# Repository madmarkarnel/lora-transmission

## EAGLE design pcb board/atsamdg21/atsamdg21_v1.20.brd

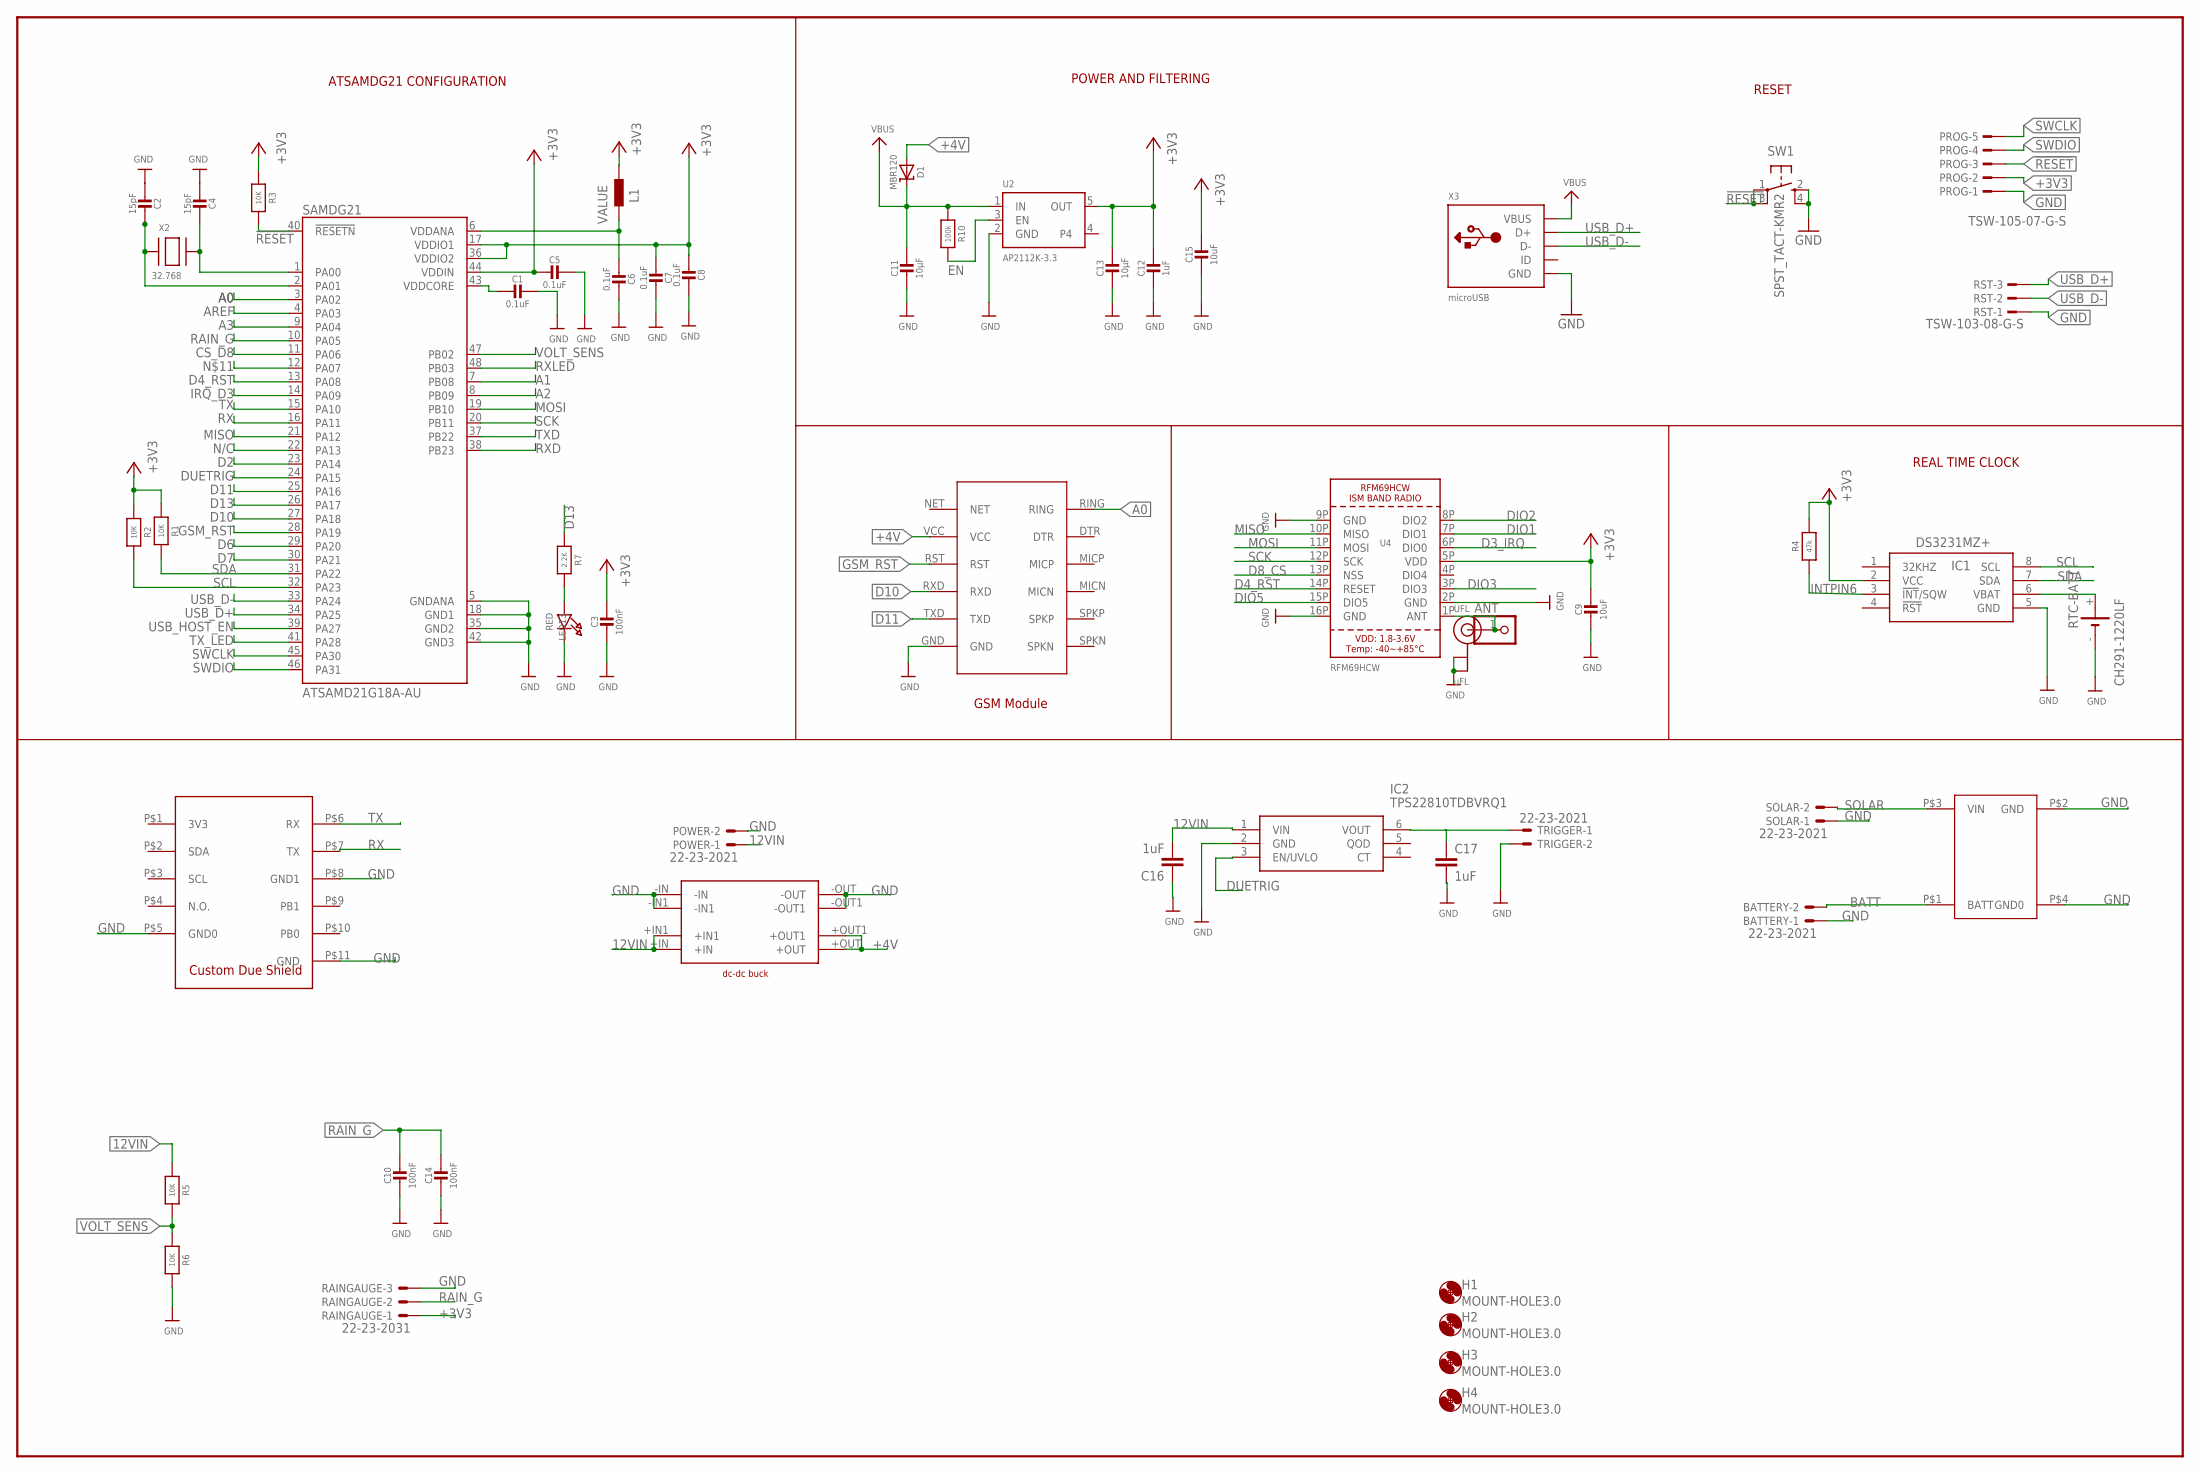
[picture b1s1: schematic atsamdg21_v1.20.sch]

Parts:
ANT: HEADER-1X1ROUND; 1X01_ROUND
BATTERY: 22-23-2021
C1, C5, C6, C7, C8: 0.1uF; 0603-NO
C2, C4: 15pF; 0603-NO
C3, C10, C14: 100nF; 0603-NO
C9, C15: 10uF; 0805-NO
C11, C13: 10µF; 0805-NO
C12: 1uF; 0603-NO
C16, C17: 1uF; C0603
D1: MBR120; SOD-123
H1, H2, H3, H4: MOUNT-HOLE3.0; 3,0
IC1: DS3231MZ+; SOIC127P600X175-8N
IC2: TPS22810TDBVRQ1; SOT95P280X145-6N
L1: BLM15HB121SN1; 0402
LED13: RED; CHIPLED_0805_NOOUTLINE
POWER: 22-23-2021
PROG: TSW-105-07-G-S; TSW-105-XX-G-S
R1, R2, R3, R5, R6: 10K; 0603-NO
R4: 47k; 0603-NO
R7: 2.2K; 0603-NO
R10: 100k; 0603-NO
RAINGAUGE: 22-23-2031
RST: TSW-103-08-G-S; TSW-103-XX-G-S
RTC-BATT: CH291-1220LF
SAMDG21: ATSAMD21G18A-AU; QFP50P900X900X120-48N
SOLAR: 22-23-2021
SW1: SPST_TACT-KMR2; KMR2
TRIGGER: 22-23-2021
U2: AP2112K-3.3; SOT23-5
U4: RFM69HCW; RFMHCW_SMT
U$7: SIM800L_MODULE; SIM800L
U$19: DC-DC_BUCK_MAD; DC-DC_BUCK
U$20: DUE_PADSDUE_GSM; DUESHIELD_BIG
U$36: LI-ION-CHARGER; LI-ION
UFL: uFL; U.FL
X2: 32.768; XTAL3215
X3: microUSB; 4UCONN_20329_V2

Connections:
12VIN: C16.2, IC2.1 (VIN), POWER.1, R5.1, U$19.+IN, U$19.+IN1
!RESET: PROG.3, R3.2, SAMDG21.40 (!RESETN), SW1.1, SW1.3 (P1)
+3V3: C3.1, C5.2, C7.2, C8.2, C9.1, C12.1, C13.1, C15.1, IC1.2 (VCC), L1.1, PROG.2, R1.1, R2.1, R3.1, R4.2, RAINGAUGE.1, SAMDG21.17 (VDDIO1), SAMDG21.36 (VDDIO2), SAMDG21.44 (VDDIN), U2.5 (OUT), U4.5P (VDD)
+4V: D1.A, U$7.VCC, U$19.+OUT, U$19.+OUT1
A0: SAMDG21.3 (PA02), U$7.RING
A1: SAMDG21.7 (PB08)
A2: SAMDG21.8 (PB09)
A3: SAMDG21.9 (PA04)
ANT: ANT.1, U4.1P (ANT), UFL.3 (SIGNAL)
AREF: SAMDG21.4 (PA03)
BATT: BATTERY.2, U$36.P$1 (BATT)
CS_D8: SAMDG21.11 (PA06)
D2: SAMDG21.23 (PA14)
D3_IRQ: U4.6P (DIO0)
D4_RST: SAMDG21.13 (PA08), U4.14P (RESET)
D6: SAMDG21.29 (PA20)
D7: SAMDG21.30 (PA21)
D8_CS: U4.13P (NSS)
D10: SAMDG21.27 (PA18), U$7.RXD
D11: SAMDG21.25 (PA16), U$7.TXD
D13: R7.1, SAMDG21.26 (PA17)
DIO1: U4.7P (DIO1)
DIO2: U4.8P (DIO2)
DIO3: U4.3P (DIO3)
DIO5: U4.15P (DIO5)
DUETRIG: IC2.3 (EN/UVLO), SAMDG21.24 (PA15)
EN: R10.2, U2.3 (EN)
GND: BATTERY.1, C1.1, C2.2, C3.2, C4.2, C5.1, C6.1, C7.1, C8.1, C9.2, C10.2, C11.2, C12.2, C13.2, C14.2, C15.2, C16.1, C17.2, IC1.5 (GND), IC2.2 (GND), LED13.C, POWER.2, PROG.1, R6.2, RAINGAUGE.3, RST.1, RTC-BATT.-, SAMDG21.5 (GNDANA), SAMDG21.18 (GND1), SAMDG21.35 (GND2), SAMDG21.42 (GND3), SOLAR.1, SW1.2 (S), SW1.4 (S1), TRIGGER.2, U2.2 (GND), U4.2P (GND), U4.9P (GND), U4.16P (GND), U$7.GND, U$19.-IN, U$19.-IN1, U$19.-OUT, U$19.-OUT1, U$20.P$5 (GND0), U$20.P$8 (GND1), U$20.P$11 (GND), U$36.P$2 (GND), U$36.P$4 (GND0), UFL.1 (GND), UFL.2 (GND), X3.BASE@1 (GND), X3.BASE@2 (GND), X3.GND, X3.SPRT@1 (GND), X3.SPRT@2 (GND), X3.SPRT@3 (GND), X3.SPRT@4 (GND)
GSM_RST: SAMDG21.28 (PA19), U$7.RST
INTPIN6: IC1.3 (!INT!/SQW), R4.1
IRQ_D3: SAMDG21.14 (PA09)
MISO: SAMDG21.21 (PA12), U4.10P (MISO)
MOSI: SAMDG21.19 (PB10), U4.11P (MOSI)
unnamed: C1.2, SAMDG21.43 (VDDCORE)
unnamed: IC1.6 (VBAT), RTC-BATT.+
unnamed: C6.2, L1.2, SAMDG21.6 (VDDANA)
unnamed: C2.1, SAMDG21.2 (PA01), X2.P$1
unnamed: C17.1, IC2.6 (VOUT), TRIGGER.1
unnamed: C4.1, SAMDG21.1 (PA00), X2.P$2
unnamed: LED13.A, R7.2
N/C: SAMDG21.22 (PA13)
RAIN_G: C10.1, C14.1, RAINGAUGE.2, SAMDG21.10 (PA05)
RX: SAMDG21.16 (PA11), U$20.P$7 (TX)
RXD: SAMDG21.38 (PB23)
RXLED: SAMDG21.48 (PB03)
SCK: SAMDG21.20 (PB11), U4.12P (SCK)
SCL: IC1.8 (SCL), R2.2, SAMDG21.32 (PA23)
SDA: IC1.7 (SDA), R1.2, SAMDG21.31 (PA22)
SOLAR: SOLAR.2, U$36.P$3 (VIN)
SWCLK: PROG.5, SAMDG21.45 (PA30)
SWDIO: PROG.4, SAMDG21.46 (PA31)
TX: SAMDG21.15 (PA10), U$20.P$6 (RX)
TXD: SAMDG21.37 (PB22)
TX_LED: SAMDG21.41 (PA28)
USB_D+: RST.3, SAMDG21.34 (PA25), X3.D+
USB_D-: RST.2, SAMDG21.33 (PA24), X3.D-
USB_HOST_EN: SAMDG21.39 (PA27)
VBUS: C11.1, D1.C, R10.1, U2.1 (IN), X3.VBUS
VOLT_SENS: R5.2, R6.1, SAMDG21.47 (PB02)

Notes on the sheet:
GSM Module
POWER AND FILTERING
RESET
ATSAMDG21 CONFIGURATION
REAL TIME CLOCK

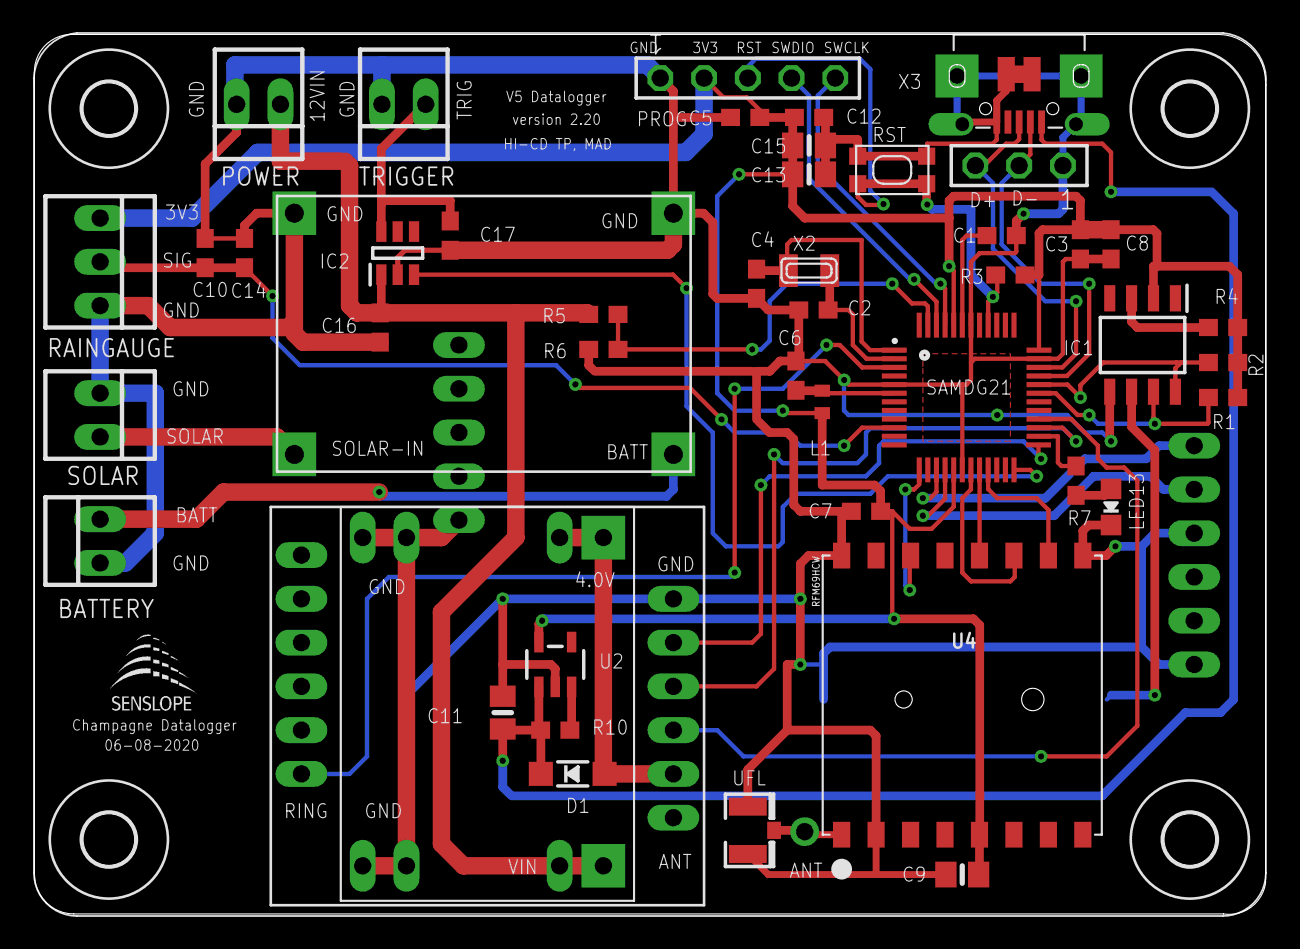
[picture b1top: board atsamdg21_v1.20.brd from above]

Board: 2 copper layers, 71.5 x 51.1 mm, 55 parts (1 on the bottom side), 38 nets.

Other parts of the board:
U$24: LOGO_SML_TNAME

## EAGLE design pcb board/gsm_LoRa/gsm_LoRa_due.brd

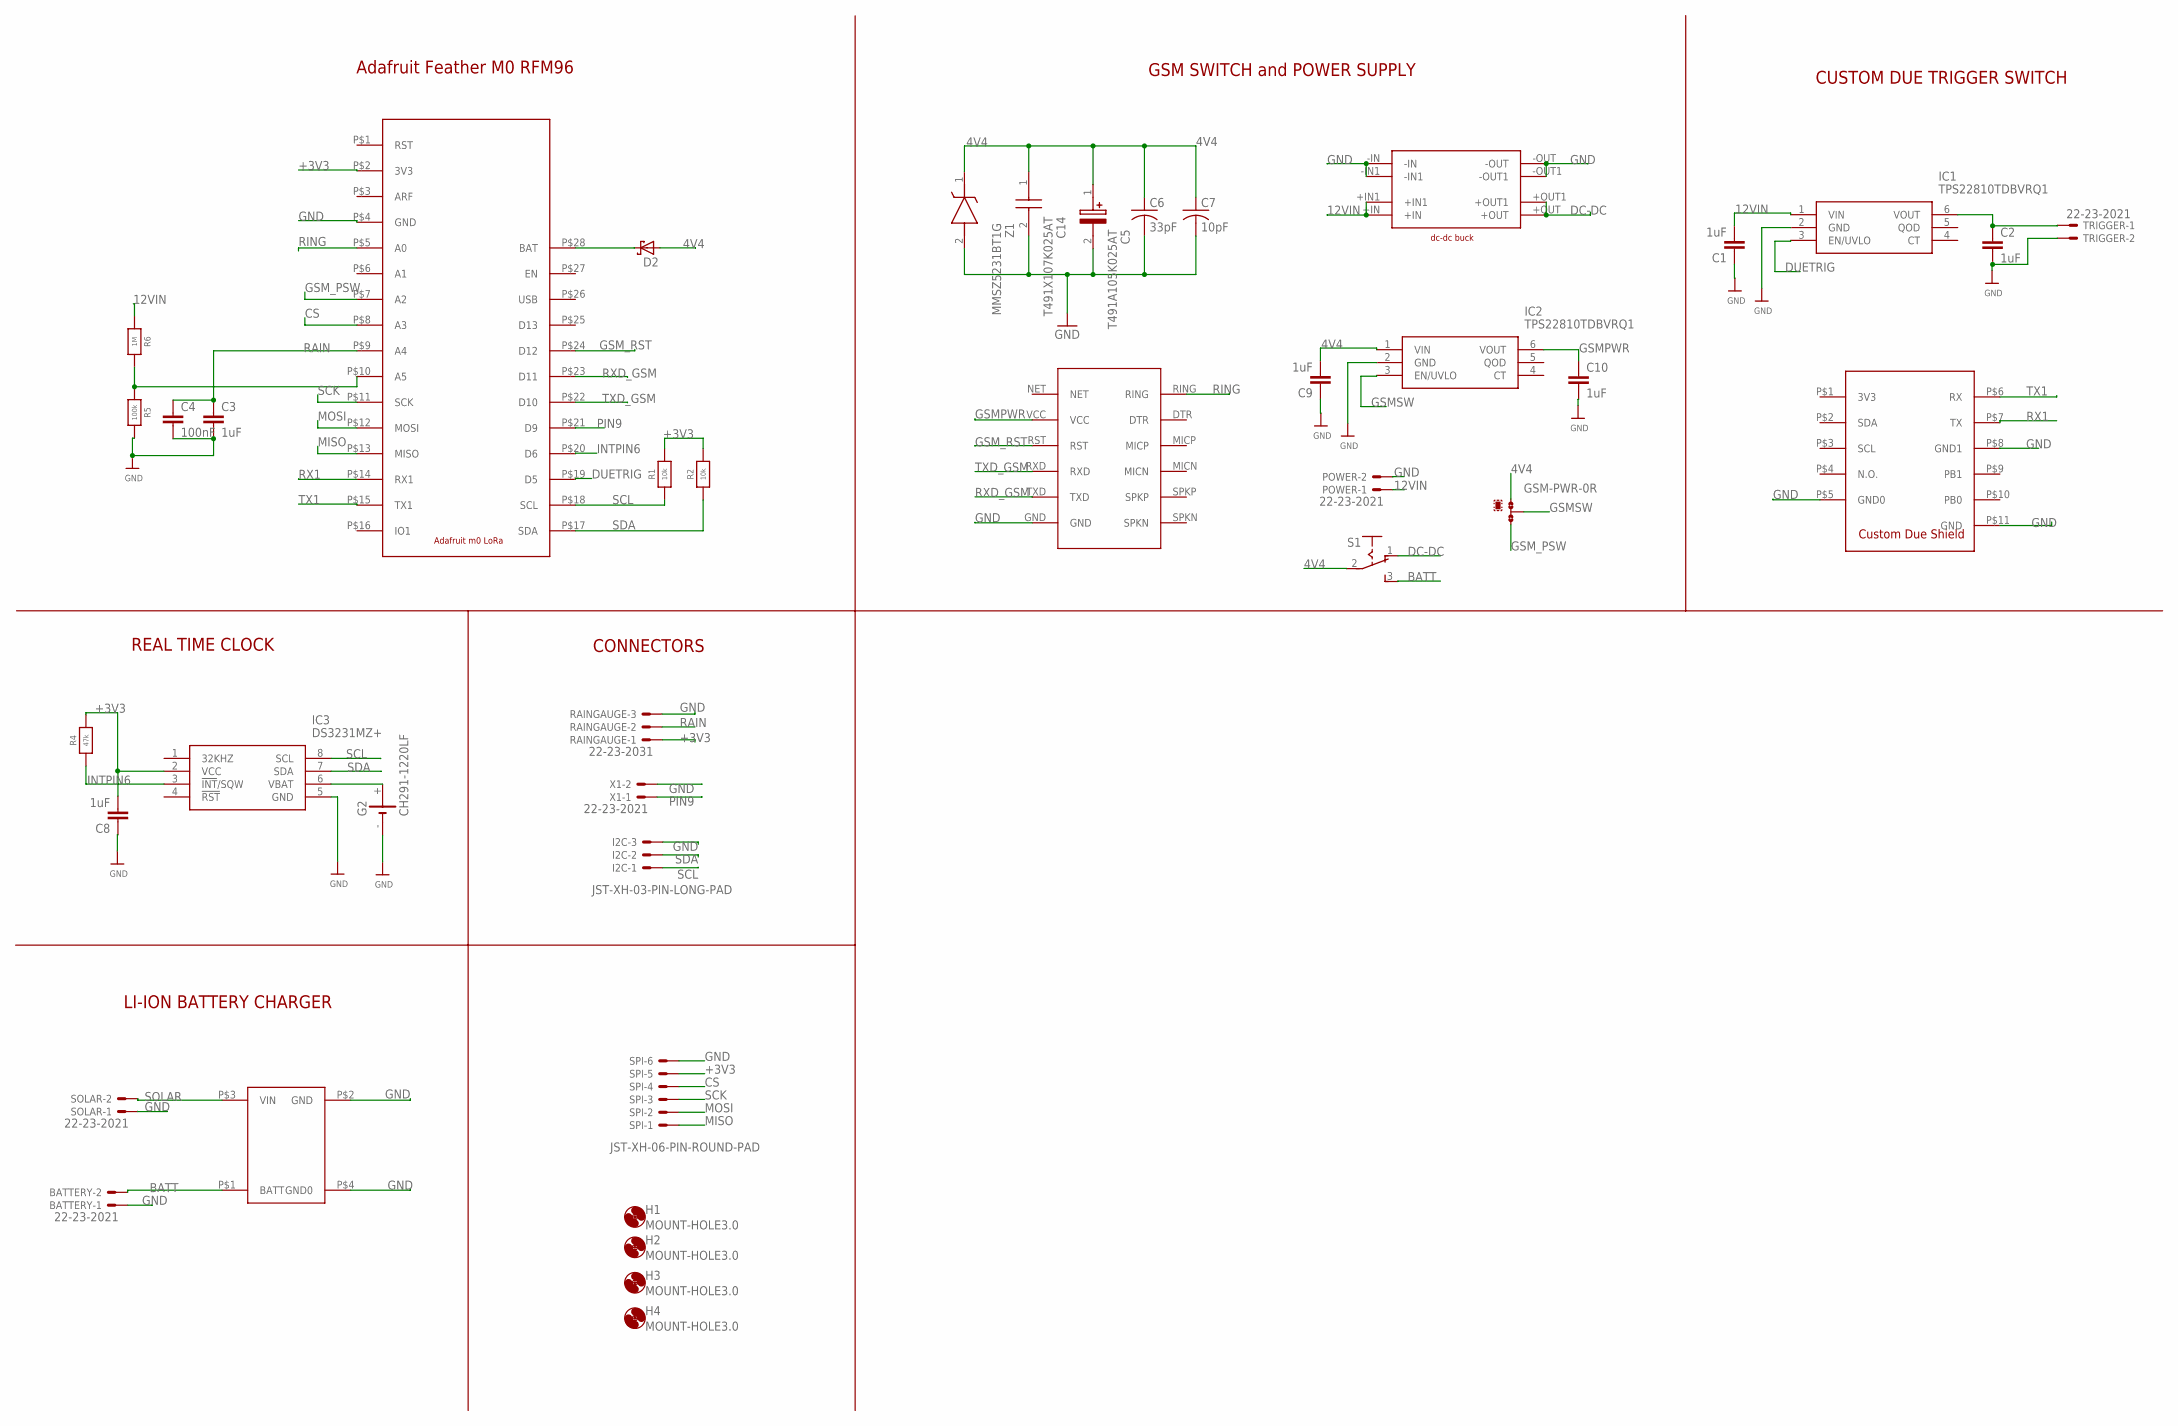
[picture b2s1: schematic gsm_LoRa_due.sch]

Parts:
BATTERY: 22-23-2021
C1, C2, C3, C8, C9, C10: 1uF; C0603
C4: 100nF; C0603
C5: T491A105K025AT; CAPPM3216X180N
C6: 33pF; C0603
C7: 10pF; C0603
C14: T491X107K025AT; CAPPM7343X430N
D2: SCHOTTKY-DIODE; DIODE_SMB
G2: CH291-1220LF
GSM-PWR: 0R-JUMPB; B0R-JMP
H1, H2, H3, H4: MOUNT-HOLE3.0; 3,0
I2C: JST-XH-03-PIN-LONG-PAD; JST-XH-03-PACKAGE-LONG-PAD
IC1, IC2: TPS22810TDBVRQ1; SOT95P280X145-6N
IC3: DS3231MZ+; SOIC127P600X175-8N
POWER: 22-23-2021
R1, R2: 10k; 0603-NO
R4: 47k; 0603-NO
R5: 100k; 0603-NO
R6: 1M; 0603-NO
RAINGAUGE: 22-23-2031
S1: 255SB
SOLAR: 22-23-2021
SPI: JST-XH-06-PIN-ROUND-PAD; JST-XH-06-PACKAGE-ROUND-PAD
TRIGGER: 22-23-2021
U$1: M0_LORA; RFM69
U$8: DUE_PADSDUE_GSM; DUESHIELD_BIG
U$9: SIM800L_MODULE; SIM800L
U$10: DC-DC_BUCK_MAD; DC-DC_BUCK
U$11: LI-ION-CHARGER; LI-ION
X1: 22-23-2021
Z1: MMSZ5231BT1G; SOD3716X135N

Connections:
4V4: C5.1 (+), C6.1, C7.1, C9.2, C14.1, D2.A (C), GSM-PWR.1, IC2.1 (VIN), S1.2, Z1.1 (K)
12VIN: C1.2, IC1.1 (VIN), POWER.1, R6.1, U$10.+IN, U$10.+IN1
+3V3: C8.2, IC3.2 (VCC), R1.2, R2.2, R4.2, RAINGAUGE.1, SPI.5, U$1.P$2 (3V3)
BATT: BATTERY.2, S1.3 (S), U$11.P$1 (BATT)
CS: SPI.4, U$1.P$8 (A3)
DC-DC: S1.1 (O), U$10.+OUT, U$10.+OUT1
DUETRIG: IC1.3 (EN/UVLO), U$1.P$19 (D5)
GND: BATTERY.1, C1.1, C2.2, C3.2, C4.2, C5.2 (-), C6.2, C7.2, C8.1, C9.1, C10.2, C14.2, G2.-, I2C.3, IC1.2 (GND), IC2.2 (GND), IC3.5 (GND), POWER.2, R5.2, RAINGAUGE.3, SOLAR.1, SPI.6, TRIGGER.2, U$1.P$4 (GND), U$8.P$5 (GND0), U$8.P$8 (GND1), U$8.P$11 (GND), U$9.GND, U$10.-IN, U$10.-IN1, U$10.-OUT, U$10.-OUT1, U$11.P$2 (GND), U$11.P$4 (GND0), X1.2, Z1.2 (A)
GSMPWR: C10.1, IC2.6 (VOUT), U$9.VCC
GSMSW: GSM-PWR.2, IC2.3 (EN/UVLO)
GSM_PSW: GSM-PWR.3, U$1.P$7 (A2)
GSM_RST: U$1.P$24 (D12), U$9.RST
INTPIN6: IC3.3 (!INT!/SQW), R4.1, U$1.P$20 (D6)
MISO: SPI.1, U$1.P$13 (MISO)
MOSI: SPI.2, U$1.P$12 (MOSI)
unnamed: D2.C (A), U$1.P$28 (BAT)
unnamed: G2.+, IC3.6 (VBAT)
unnamed: R5.1, R6.2, U$1.P$10 (A5)
unnamed: C2.1, IC1.6 (VOUT), TRIGGER.1
PIN9: U$1.P$21 (D9), X1.1
RAIN: C3.1, C4.1, RAINGAUGE.2, U$1.P$9 (A4)
RING: U$1.P$5 (A0), U$9.RING
RX1: U$1.P$14 (RX1), U$8.P$7 (TX)
RXD_GSM: U$1.P$23 (D11), U$9.TXD
SCK: SPI.3, U$1.P$11 (SCK)
SCL: I2C.1, IC3.8 (SCL), R1.1, U$1.P$18 (SCL)
SDA: I2C.2, IC3.7 (SDA), R2.1, U$1.P$17 (SDA)
SOLAR: SOLAR.2, U$11.P$3 (VIN)
TX1: U$1.P$15 (TX1), U$8.P$6 (RX)
TXD_GSM: U$1.P$22 (D10), U$9.RXD

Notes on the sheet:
Adafruit Feather M0 RFM96
GSM SWITCH and POWER SUPPLY
CUSTOM DUE TRIGGER SWITCH
REAL TIME CLOCK
CONNECTORS
LI-ION BATTERY CHARGER

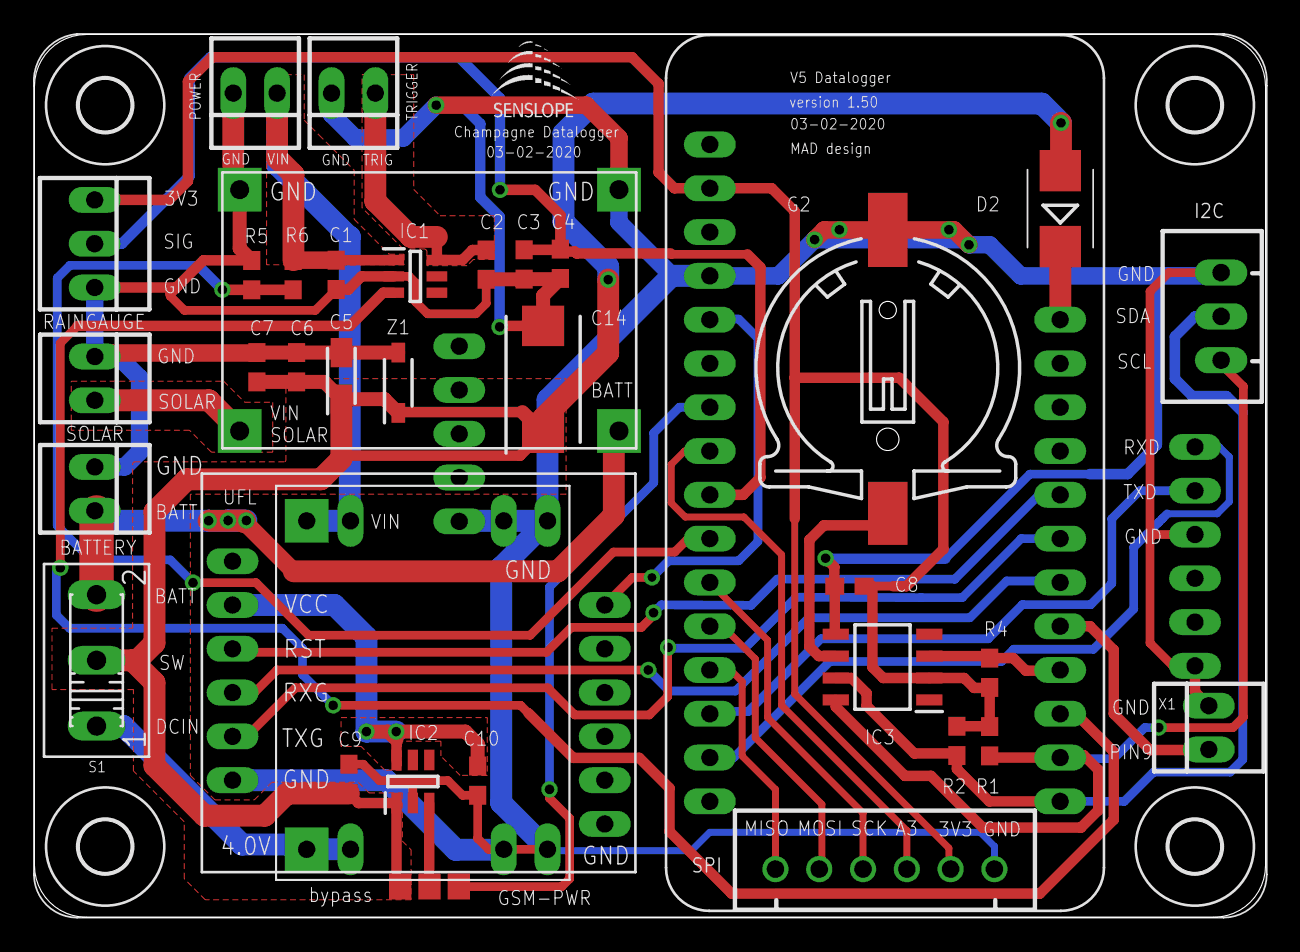
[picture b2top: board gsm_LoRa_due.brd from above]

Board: 2 copper layers, 71.4 x 51.2 mm, 42 parts (0 on the bottom side), 30 nets.

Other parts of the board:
U$13: LOGO_SML_TNAME

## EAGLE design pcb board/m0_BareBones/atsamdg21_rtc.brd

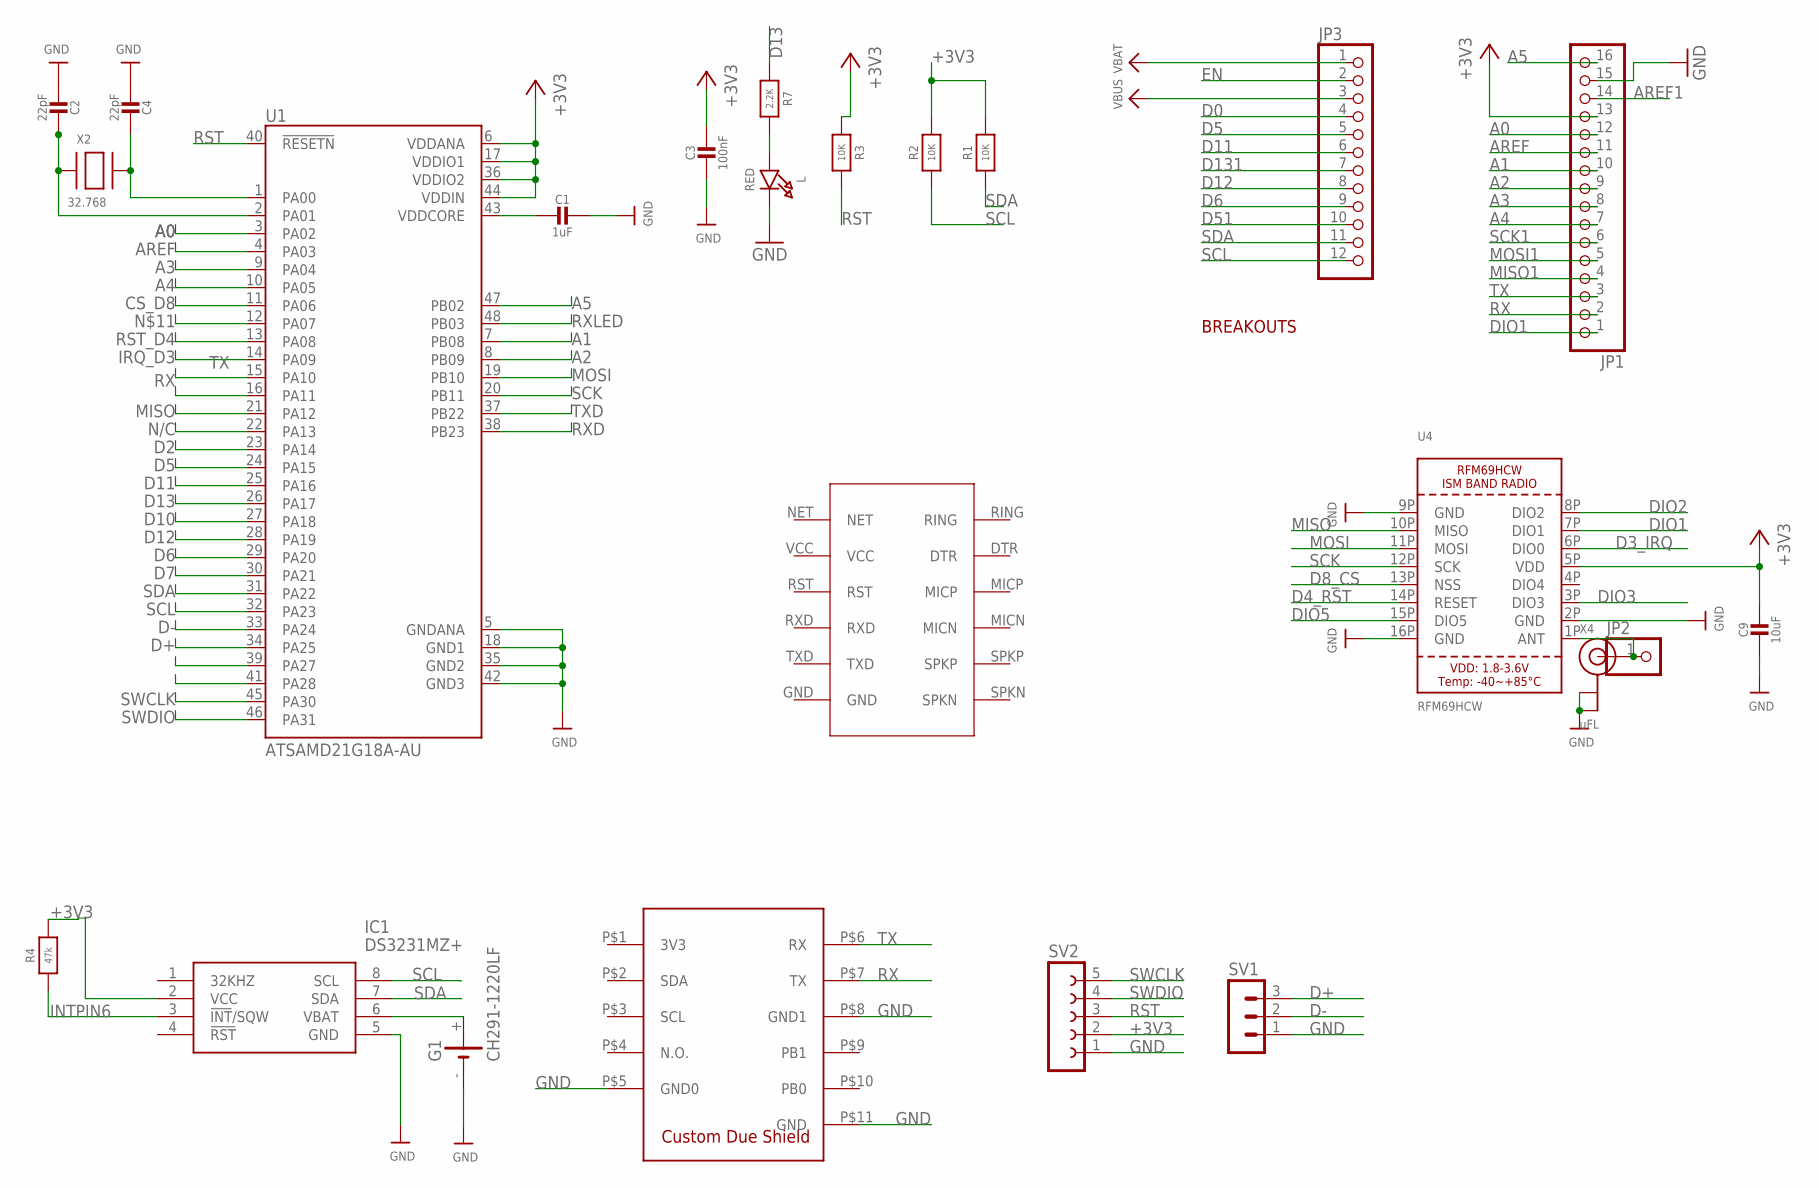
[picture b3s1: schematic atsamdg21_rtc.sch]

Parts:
C1: 1uF; 0603-NO
C2, C4: 22pF; 0603-NO
C3: 100nF; 0603-NO
C9: 10uF; 0805-NO
G1: CH291-1220LF
IC1: DS3231MZ+; SOIC127P600X175-8N
JP1: HEADER-1X16ROUND; 1X16_ROUND
JP2: HEADER-1X1ROUND; 1X01_ROUND
JP3: HEADER-1X12; 1X12_ROUND
L: RED; CHIPLED_0805_NOOUTLINE
R1, R2, R3: 10K; 0603-NO
R4: 47k; 0603-NO
R7: 2.2K; 0603-NO
SV1: MA03-1
SV2: FE05-1
U1: ATSAMD21G18A-AU; QFP50P900X900X120-48N
U4: RFM69HCW; RFMHCW_SMT
U$7: SIM800L_MODULE; SIM800L
U$9: DUE_PADS; DUESHIELD
X2: 32.768; XTAL3215
X4: uFL; U.FL

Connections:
+3V3: C3.1, C9.1, IC1.2 (VCC), JP1.13, R1.2, R2.2, R3.1, R4.2, SV2.2, U1.6 (VDDANA), U1.17 (VDDIO1), U1.36 (VDDIO2), U1.44 (VDDIN), U4.5P (VDD)
A0: JP1.12, U1.3 (PA02)
A1: JP1.10, U1.7 (PB08)
A2: JP1.9, U1.8 (PB09)
A3: JP1.8, U1.9 (PA04)
A4: JP1.7, U1.10 (PA05)
A5: JP1.16, U1.47 (PB02)
ANT: JP2.1, U4.1P (ANT), X4.3 (SIGNAL)
AREF: JP1.11, U1.4 (PA03)
AREF1: JP1.14
CS_D8: U1.11 (PA06)
D0: JP3.4
D2: U1.23 (PA14)
D3_IRQ: U4.6P (DIO0)
D4_RST: U4.14P (RESET)
D5: JP3.5, U1.24 (PA15)
D6: JP3.9, U1.29 (PA20)
D7: U1.30 (PA21)
D8_CS: U4.13P (NSS)
D10: U1.27 (PA18)
D11: JP3.6, U1.25 (PA16)
D12: JP3.8, U1.28 (PA19)
D13: R7.1, U1.26 (PA17)
D51: JP3.10
D131: JP3.7
D+: SV1.3, U1.34 (PA25)
D-: SV1.2, U1.33 (PA24)
DIO1: JP1.1, U4.7P (DIO1)
DIO2: U4.8P (DIO2)
DIO3: U4.3P (DIO3)
DIO5: U4.15P (DIO5)
EN: JP3.2
GND: C1.1, C2.2, C3.2, C4.2, C9.2, G1.-, IC1.5 (GND), JP1.15, L.C, SV1.1, SV2.1, U1.5 (GNDANA), U1.18 (GND1), U1.35 (GND2), U1.42 (GND3), U4.2P (GND), U4.9P (GND), U4.16P (GND), U$9.P$5 (GND0), U$9.P$8 (GND1), U$9.P$11 (GND), X4.1 (GND), X4.2 (GND)
INTPIN6: IC1.3 (!INT!/SQW), R4.1
IRQ_D3: U1.14 (PA09)
MISO: U1.21 (PA12), U4.10P (MISO)
MISO1: JP1.4
MOSI: U1.19 (PB10), U4.11P (MOSI)
MOSI1: JP1.5
unnamed: C1.2, U1.43 (VDDCORE)
unnamed: G1.+, IC1.6 (VBAT)
unnamed: C2.1, U1.2 (PA01), X2.P$1
unnamed: C4.1, U1.1 (PA00), X2.P$2
unnamed: L.A, R7.2
N/C: U1.22 (PA13)
RST: R3.2, SV2.3, U1.40 (!RESETN)
RST_D4: U1.13 (PA08)
RX: JP1.2, U1.16 (PA11), U$9.P$7 (TX)
RXD: U1.38 (PB23)
RXLED: U1.48 (PB03)
SCK: U1.20 (PB11), U4.12P (SCK)
SCK1: JP1.6
SCL: IC1.8 (SCL), JP3.12, R2.1, U1.32 (PA23)
SDA: IC1.7 (SDA), JP3.11, R1.1, U1.31 (PA22)
SWCLK: SV2.5, U1.45 (PA30)
SWDIO: SV2.4, U1.46 (PA31)
TX: JP1.3, U1.15 (PA10), U$9.P$6 (RX)
TXD: U1.37 (PB22)
VBAT: JP3.1
VBUS: JP3.3

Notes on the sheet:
BREAKOUTS

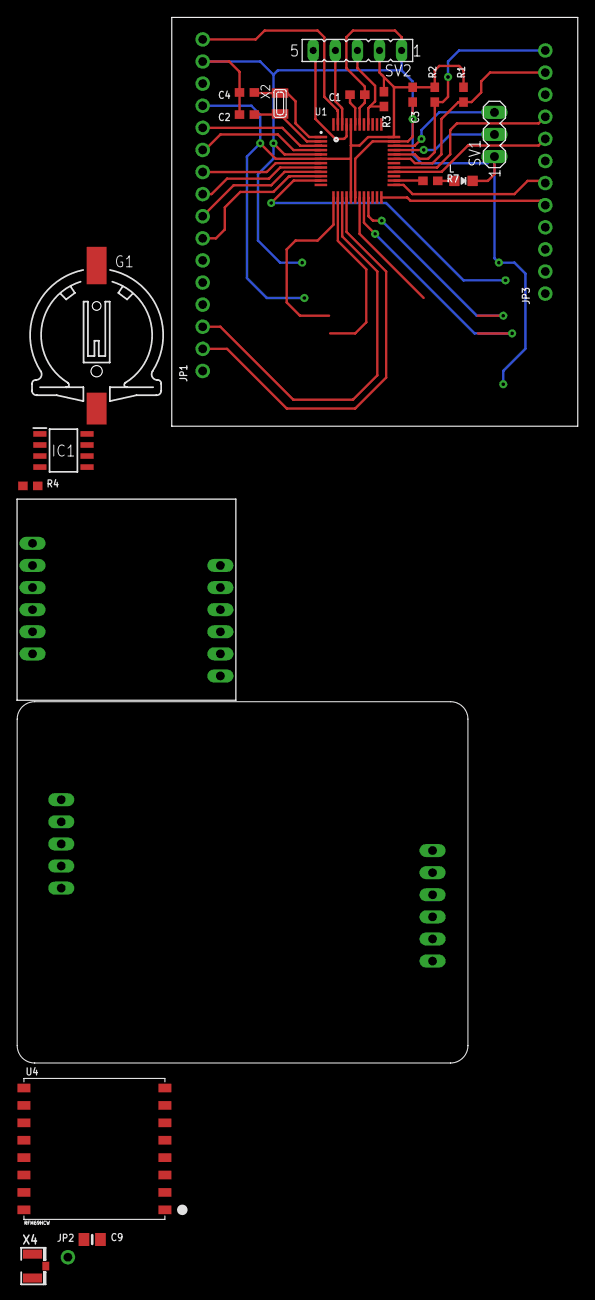
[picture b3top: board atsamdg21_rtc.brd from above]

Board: 2 copper layers, 46.7 x 47.0 mm, 24 parts (0 on the bottom side), 34 nets.

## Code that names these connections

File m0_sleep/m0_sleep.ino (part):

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#define DUEBAUD 9600
#define DUESerial Serial1
#define RTCINTPIN 6
#define DUETRIG 5
#define RSTMCU 9
#define DEBUG 1
#define VBATPIN A7
#define VBATEXT A5
#define GSMRST 12
#define GSMPWR A2
#define GSMDTR A1
#define GSMINT A0 //gsm ring interrupt

//gsm related
#define GSMBAUDRATE 9600
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  init_lora();

  pinMode(LED_BUILTIN, OUTPUT);
  pinMode(DUETRIG, OUTPUT);
  pinMode(GSMPWR, OUTPUT);
  pinMode(GSMRST, OUTPUT);
  pinMode(RSTMCU, OUTPUT); //MCU hard reset pin

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
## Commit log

2018-12-03 update code
2018-12-03 tx update
2019-05-19 working sleep functions for m0
2019-05-19 works with m0 init LoRa
2019-05-19 LoRa updates
2019-05-28 working low power ~100uA sleep current working due to m0 serial
2019-05-31 added no data from sensors added alarm every 0,5,10,15 ; 30,35,40,45 ;ABCD added Debug Mode before startUp
2019-05-31 updated Debug mode
2019-07-22 working rtc hard setting interval in interrupt wakeUp
2019-07-25 -working flash memory; saves sending interval & senslope commandto flashMem -user setting can be updated from serial
2019-07-25 -added sensor name in flash memory -access sensor name in no data from senslope
2019-07-29 - updated alarmFlashMemory function - working debug mode (can edit alarm interval and senslope command) - removed duplicate functions - update syntax format
2019-08-01 -setting time of data logger -syncs time from PC
2019-08-02 - updated code to python 3
2019-08-07 -updated to python 3 -update serial.close() function
2019-08-08 -working sending message thru sim800L
2019-08-23 - added timestamp on command - removed timestamp after received data - working with custom due
2019-08-23 -updated print functions
2019-09-18 - added RSSI value checker - default to 900MHz ;
2019-09-19 - IndexError: list index out of range - print("RTC", ts[2].decode('ascii').strip())
2019-10-01 Arabica Datalogger - working all functions - RTC alarm interrupt - low power LoRa, ~1uA sleep mode
2019-10-01 - default to 900MHz
2019-10-01 - added EEPROM saving functions - based on ARABICA Datalogger - working all functionalities
2019-10-01 - pdu not yet working
2019-10-04 arabica.ino - fixed bug: sampling data after exiting debug mode and once turned ON without debug mode
2019-11-06 -updated to 433Mhz default frequency
2019-11-18 - added battery voltage monitor sending
2019-11-25 working serial2 from pin 10 and 11 sim800 working
2019-11-26 - added "<<" after the end of data string
2020-01-14 - working 2 interrupt (rtc and rain gauge) - sleep mode when no rain detected - resets rain after sending sensor data
2020-01-14 - working sending gsm sms
2020-01-17 - working gsm sleep mode ~1mA - gsm funtions in different folder - working rain gauge interrupt
2020-01-23 - working rain and sensor interrupt
2020-01-23 csq =
2020-01-27 - updated to python 3
2020-01-28 - updated message string for rain text
2020-01-29 detect "OK" and "ERROR" using regexp
2020-01-29 detect "CSQ: " response
2020-02-03 - not working reciv LoRa
2020-02-05 add new gsm functions try getcsq function
2020-02-06 - sends rain data and custom due data - added mode 5 in rtc alarm every 5, 15, 25 . . . - not sending LoRa data yet
2020-02-07 Working all features 1. Send rain tips interrupt 2. Get due data 3. Receive LoRa data from remote
2020-02-07 - fixed white space "\r" after site name
2020-02-08 sms sending retry
2020-02-10 Added logger version in Flash Memory
2020-02-10 Saves server number in flash memory but not yet working
2020-02-12 working code for v5 datalogger, v5 LoRa transmitter, arabica
2020-02-12 modify send and read sms
2020-02-13 Working gsm send message from flash memory number
2020-02-14 Removed white space "\r" in gsm message to send. Working gsm.
2020-02-14 measure battery voltage update
2020-02-14 Added voltage parsing
2020-02-14 Updated functions
2020-02-18 Working get rssi from LoRa transmitter
2020-02-19 add function for changing parameters
2020-02-20 changes in debug mode
2020-02-21 combine print and change
2020-02-21 change letters like arq
2020-02-27 pcb boards
2020-02-28 added SPI connector
2020-02-28 barebones atsamd21
2020-03-02 check ok response for wake and sleep functions
2020-03-02 Updated names on traces
2020-03-03 Added power IC switch for GSM Updated names of components
2020-03-05 Edited via size
2020-03-06 added gsm reset, power ON and power OFF
2020-03-06 Added reset
2020-03-06 updated traces and polygon
2020-03-06 update gsmManualconnect
2020-03-09 Input names of remote dataloggers
2020-03-11 rssi of 2 tx working; Gateway mode
2020-03-12 working datalogger mode 4 2 LoRa transmitter
2020-04-15 *Updated sending_thru_gsm - sending failed availble when gsm not connected *getCSQ - faster getting csq - 99 no csq available
2020-04-15 updated for v5 setting dateTime
2020-04-17 *Updated parsing voltage *Added 3 receiver and sensor name *Added special case for MAR (send sensor and rain data via LoRa)
2020-05-04 - sample embedded board
2020-05-05 working sms receive command interrupt when ring
2020-05-05 addded ring pin to A0
2020-05-15 update 05/15
2020-05-22 05/22 update
2020-05-22 -updated usb pin connections, overlap, ground plane bottom
2020-05-29 - fixed bug in sending sms - auto connect sim network depending on stored number - faster csq reading
2020-05-29 update 05/29
2020-06-02 - updated saving names in memory - gsm over the air commands working
2020-06-05 v5autoconfig.py: new script, automatic config setup for v5
2020-06-09 -updated
2020-06-09 - updated traces - added ring gsm connection
2020-06-09 v5autoconfig; create new folder for script v5autoconfig/v5autoconfig.zip = complete copy v5autoconfig.py = main script datav5config.csv = config settings docuv5autoconfig.txt = documentation
2020-06-10 -added gsm ring functions -updated routing
2020-06-10 v5autoconfig/v5autoconfig.py; force obtain debug mode
2020-06-10 v5autoconfig/v5autoconfig.zip; update script
2020-06-11 v5autoconfig/ add new functions: loggername, mcupassword, sensorcommand
2020-06-12 -upadated rain data sending
2020-06-18 update 06192020
    Major changes:
    Added timeout for non-responding serial write commands.
    Implemented csv checking before mcu programming.
    Included error raising for csv input errors.
    Extended set datetime functionality to set timestamp in the format YYYY-MM-DD HH:MM:SS.
    Minor:
2020-06-18 v5troubleshooter.py;
    for v5 semi-automated troubleshooting
2020-06-26 update 06262020
    Major changes:
    1. added datetime and battery voltage readout
    2. validation of received csq, voltage, and timestamp data
    3. draft function for sensor trigger.
    Minor changes:
    1. added print parameter for text finding function
2020-06-30 Gerber files, assembly
2020-06-30 bluetooth tx/rx
2020-07-02 update 070220
    Added sms test process.
    Included dependency of test processes to logger version.
2020-07-04 update 070420
    Major changes:
    Use json file to store config settings and data logs, filename will contain site name, personnel name, and timestamp
    Retrieve config settings before running test processes: servernum, loggerversion, sendingtime, mcupassword, loggernames, sensorcommand
    Minor changes:
    Replace undecodeable serial characters with '?'
    Add additional CSQ sampling to obtain odd number of samples for median computation
2020-07-10 update 071020
    Major changes:
    Integrated supply of solutions for known v5 problems
    Simplified all getters to general get_config function
    Included 'about' parameter to hold datalogger name, personnel, and timestamp
    Included 'result' and 'solution' parameter in log file
    Categorized result as "PASS" or "FAIL"
2020-07-18 update 071520
    Major changes:
    Implement averaging for voltage sampling
    Minor changes:
    Update csq solution message
2020-07-18 fanout comport detection process update from v5troubleshooter
2020-08-18 Added IMU sensors in V5 dataloggers
2020-09-14 Updated IMU code - data string - added to menu (LoRa or GSM)
2020-09-15 IMU functions - added flash memory parameters - get raw data function using memory allocation - calibrated data function
2020-09-21 -added power pin for IMU (power ON on wakeUp and power OFF on sleep) -added temp on IMU string
2020-09-28 Updated IMU get data functions
2020-10-08 -added temperature in IMU data -add flash memory storage for IMU calib or raw data parameters -fixed voltage reading error in surficial tilt mode(PIN 9 is not usable if used as VBAT reading) -updated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
2020-10-19 -updated turning on GSM and manual GSM connect -interchanged sending of IMU data and rain data
2020-10-23 -updated power pin of IMU -delay_millis function added (using millis() not delay) -updated GSM wakeup timeout
2020-11-15 -common sensor sampling commands -added rain gauge only datalogger version(11)
2021-02-03 -added GSM power selector (sleep, always ON, OFF/ON) -change GSM baud rate to 115200 -updated GSM reset function -updated menu selection
2021-02-04 -updated UI of debug menu for readability -fixed storing of data in flash memory (names, password etc.) -fixed manual GSM commands -fixed error in parsing GSM reply buffer
2021-02-09 -refactored OTA commands
2021-02-17 branch copy: watchdog experiment *enable watchdog on main loop *disable watchdog for processes estimated to go beyond 16s: turn_ON_GSM receive_lora_data send_rain_data get_Due_Data
2021-02-19 -added additional server numbers -read rain gauge as whole number
2021-02-19 Added new parameter: gsmpowmode Added new exception to be raised for unresponsive device. Added error message for mcu timestamp readout that begins with '65' Updated message display. Added gsmpowmode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
2021-02-22 - added 5 minutes timeout to exit debug menu - added reset at the start of the program - added current firmware version in menu - updated menu UI
2021-03-10 - updated initialization setting of gsm - added: reset gsm when sending failed - added OTA functions - add watchdog timer
2021-03-10 - added watchdog timers= in each logger functions - added print config parameters in debug menu - refactored getting logger voltage - refactored parsing function in receiving LoRa
2021-03-10 - added disable watchdog timers in debug mode - updated functions

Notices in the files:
parts and their libraries:
microbuilder: This work is placed in the public domain, and may be freely used for commercial and non-commercial work with the following conditions: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
